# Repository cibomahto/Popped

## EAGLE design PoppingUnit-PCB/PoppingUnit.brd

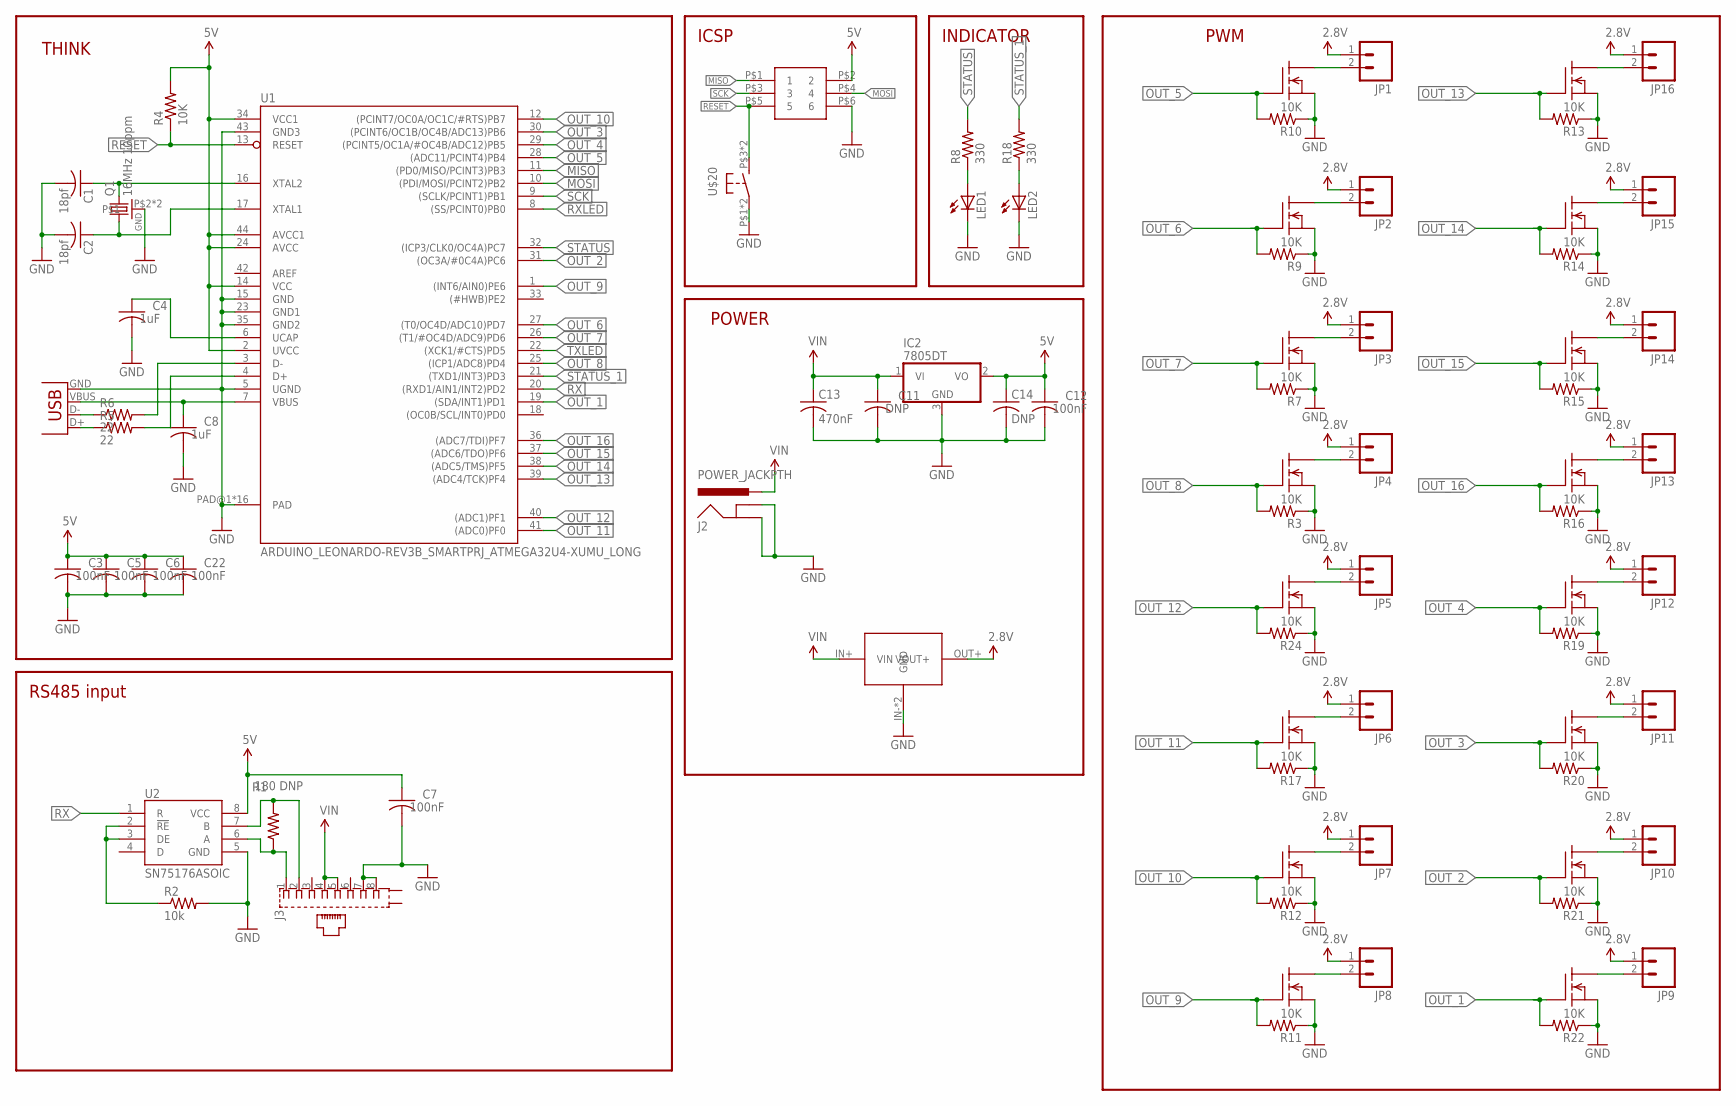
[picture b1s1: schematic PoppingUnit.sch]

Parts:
C1, C2: 18pf; C0603K
C3, C5, C6, C7, C12, C22: 100nF; C0603K
C4, C8: 1uF; C0603K
C11, C14: DNP; C0603K
C13: 470nF; C0603K
IC2: 7805DT; TO252
J2: POWER_JACKPTH; POWER_JACK_PTH
J3: 555153-1
JP1, JP2, JP3, JP4, JP5, JP6, JP7, JP8, JP9, JP10, JP11, JP12, JP13, JP14, JP15, JP16: M02-JST-2-PTH-NO_SILK; JST-2-PTH-NS
LED1, LED2: LED5MM
Q1: 16MHz 10ppm; CRSYTAL_2520
R1: 180 DNP; R0603
R2: 10k; R0603
R3, R4, R7, R9, R10, R11, R12, R13, R14, R15, R16, R17, R19, R20, R21, R22, R24: 10K; R0603
R5, R6: 22; R0603
R8, R18: 330; R0603
U1: ARDUINO_LEONARDO-REV3B_SMARTPRJ_ATMEGA32U4-XUMU_L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; QFN44ML7X7_LONGLEADS
U2: SN75176ASOIC; SO08
U$1, U$3, U$4, U$5, U$6, U$7, U$8, U$9, U$10, U$11, U$12, U$14, U$15, U$16, U$17, U$18: N_MOSFET; TO252
U$2: 2X3HEADER
U$19: DC_DC; DSN2596
U$20: BUTTON_MOMENTARY; BUTTON_MOMENTARY_KMR211G
X1: USBPTH; USB-B-PTH

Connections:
2.8V: JP1.1, JP2.1, JP3.1, JP4.1, JP5.1, JP6.1, JP7.1, JP8.1, JP9.1, JP10.1, JP11.1, JP12.1, JP13.1, JP14.1, JP15.1, JP16.1, U$19.OUT+ (VOUT+)
5V: C3.1, C5.1, C6.1, C7.1, C12.1, C14.1, C22.1, IC2.2 (VO), R4.2, U1.2 (UVCC), U1.14 (VCC), U1.24 (AVCC), U1.34 (VCC1), U1.44 (AVCC1), U2.8 (VCC), U$2.P$2 (2)
AREF: U1.42 (AREF)
CONNECT_ME: R2.1, U2.2 (!RE), U2.3 (DE)
GND: C1.2, C2.2, C3.2, C4.2, C5.2, C6.2, C7.2, C8.2, C11.2, C12.2, C13.2, C14.2, C22.2, IC2.3 (GND), J2.GND, J2.GNDBREAK, J3.7, J3.8, LED1.K (C), LED2.K (C), Q1.P$2, Q1.P$4, R2.2, R3.1, R7.1, R9.1, R10.1, R11.1, R12.1, R13.1, R14.1, R15.1, R16.1, R17.1, R19.1, R20.1, R21.1, R22.1, R24.1, U1.5 (UGND), U1.15 (GND), U1.23 (GND1), U1.35 (GND2), U1.43 (GND3), U1.PAD@1 (PAD), U1.PAD@2 (PAD), U1.PAD@3 (PAD), U1.PAD@4 (PAD), U1.PAD@5 (PAD), U1.PAD@6 (PAD), U1.PAD@7 (PAD), U1.PAD@8 (PAD), U1.PAD@9 (PAD), U1.PAD@10 (PAD), U1.PAD@11 (PAD), U1.PAD@12 (PAD), U1.PAD@13 (PAD), U1.PAD@14 (PAD), U1.PAD@15 (PAD), U1.PAD@16 (PAD), U2.5 (GND), U$1.P$2 (S), U$2.P$6 (6), U$3.P$2 (S), U$4.P$2 (S), U$5.P$2 (S), U$6.P$2 (S), U$7.P$2 (S), U$8.P$2 (S), U$9.P$2 (S), U$10.P$2 (S), U$11.P$2 (S), U$12.P$2 (S), U$14.P$2 (S), U$15.P$2 (S), U$16.P$2 (S), U$17.P$2 (S), U$18.P$2 (S), U$19.IN- (GND), U$19.OUT- (GND), U$20.P$1, U$20.P$2, X1.GND
MISO: U1.11 ((PD0/MISO/PCINT3)PB3), U$2.P$1 (1)
MOSI: U1.10 ((PDI/MOSI/PCINT2)PB2), U$2.P$4 (4)
unnamed: R6.1, X1.D-
unnamed: C1.1, Q1.P$3 (2), U1.16 (XTAL2)
unnamed: R5.1, X1.D+
unnamed: R5.2, U1.4 (D+)
unnamed: C2.1, Q1.P$1 (1), U1.17 (XTAL1)
unnamed: R6.2, U1.3 (D-)
unnamed: C8.1, U1.7 (VBUS), X1.VBUS
unnamed: LED1.A, R8.1
unnamed: C4.1, U1.6 (UCAP)
unnamed: JP11.2, U$16.P$3 (D)
unnamed: JP1.2, U$1.P$3 (D)
unnamed: LED2.A, R18.1
unnamed: JP2.2, U$3.P$3 (D)
unnamed: JP3.2, U$4.P$3 (D)
unnamed: JP4.2, U$5.P$3 (D)
unnamed: JP5.2, U$10.P$3 (D)
unnamed: JP6.2, U$11.P$3 (D)
unnamed: JP7.2, U$12.P$3 (D)
unnamed: JP8.2, U$14.P$3 (D)
unnamed: JP9.2, U$18.P$3 (D)
unnamed: JP10.2, U$17.P$3 (D)
unnamed: JP12.2, U$15.P$3 (D)
unnamed: JP13.2, U$9.P$3 (D)
unnamed: JP14.2, U$8.P$3 (D)
unnamed: JP15.2, U$7.P$3 (D)
unnamed: JP16.2, U$6.P$3 (D)
OUT_1: R22.2, U1.19 ((SDA/INT1)PD1), U$18.P$1 (G)
OUT_2: R21.2, U1.31 ((OC3A/#0C4A)PC6), U$17.P$1 (G)
OUT_3: R20.2, U1.30 ((PCINT6/OC1B/OC4B/ADC13)PB6), U$16.P$1 (G)
OUT_4: R19.2, U1.29 ((PCINT5/OC1A/#OC4B/ADC12)PB5), U$15.P$1 (G)
OUT_5: R10.2, U1.28 ((ADC11/PCINT4)PB4), U$1.P$1 (G)
OUT_6: R9.2, U1.27 ((T0/OC4D/ADC10)PD7), U$3.P$1 (G)
OUT_7: R7.2, U1.26 ((T1/#OC4D/ADC9)PD6), U$4.P$1 (G)
OUT_8: R3.2, U1.25 ((ICP1/ADC8)PD4), U$5.P$1 (G)
OUT_9: R11.2, U1.1 ((INT6/AIN0)PE6), U$14.P$1 (G)
OUT_10: R12.2, U1.12 ((PCINT7/OC0A/OC1C/#RTS)PB7), U$12.P$1 (G)
OUT_11: R17.2, U1.41 ((ADC0)PF0), U$11.P$1 (G)
OUT_12: R24.2, U1.40 ((ADC1)PF1), U$10.P$1 (G)
OUT_13: R13.2, U1.39 ((ADC4/TCK)PF4), U$6.P$1 (G)
OUT_14: R14.2, U1.38 ((ADC5/TMS)PF5), U$7.P$1 (G)
OUT_15: R15.2, U1.37 ((ADC6/TDO)PF6), U$8.P$1 (G)
OUT_16: R16.2, U1.36 ((ADC7/TDI)PF7), U$9.P$1 (G)
RESET: R4.1, U1.13 (RESET), U$2.P$5 (5), U$20.P$3 (S), U$20.P$4 (S)
RS485A: J3.1, R1.1, U2.6 (A)
RS485B: J3.2, R1.2, U2.7 (B)
RX: U1.20 ((RXD1/AIN1/INT2)PD2), U2.1 (R)
RXLED: U1.8 ((SS/PCINT0)PB0)
SCK: U1.9 ((SCLK/PCINT1)PB1), U$2.P$3 (3)
STATUS: R8.2, U1.32 ((ICP3/CLK0/OC4A)PC7)
STATUS_1: R18.2, U1.21 ((TXD1/INT3)PD3)
TXLED: U1.22 ((XCK1/#CTS)PD5)
VIN: C11.1, C13.1, IC2.1 (VI), J2.PWR, J3.4, J3.5, U$19.IN+ (VIN)

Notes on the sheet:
RS485 input
ICSP
INDICATOR
PWM
POWER
THINK

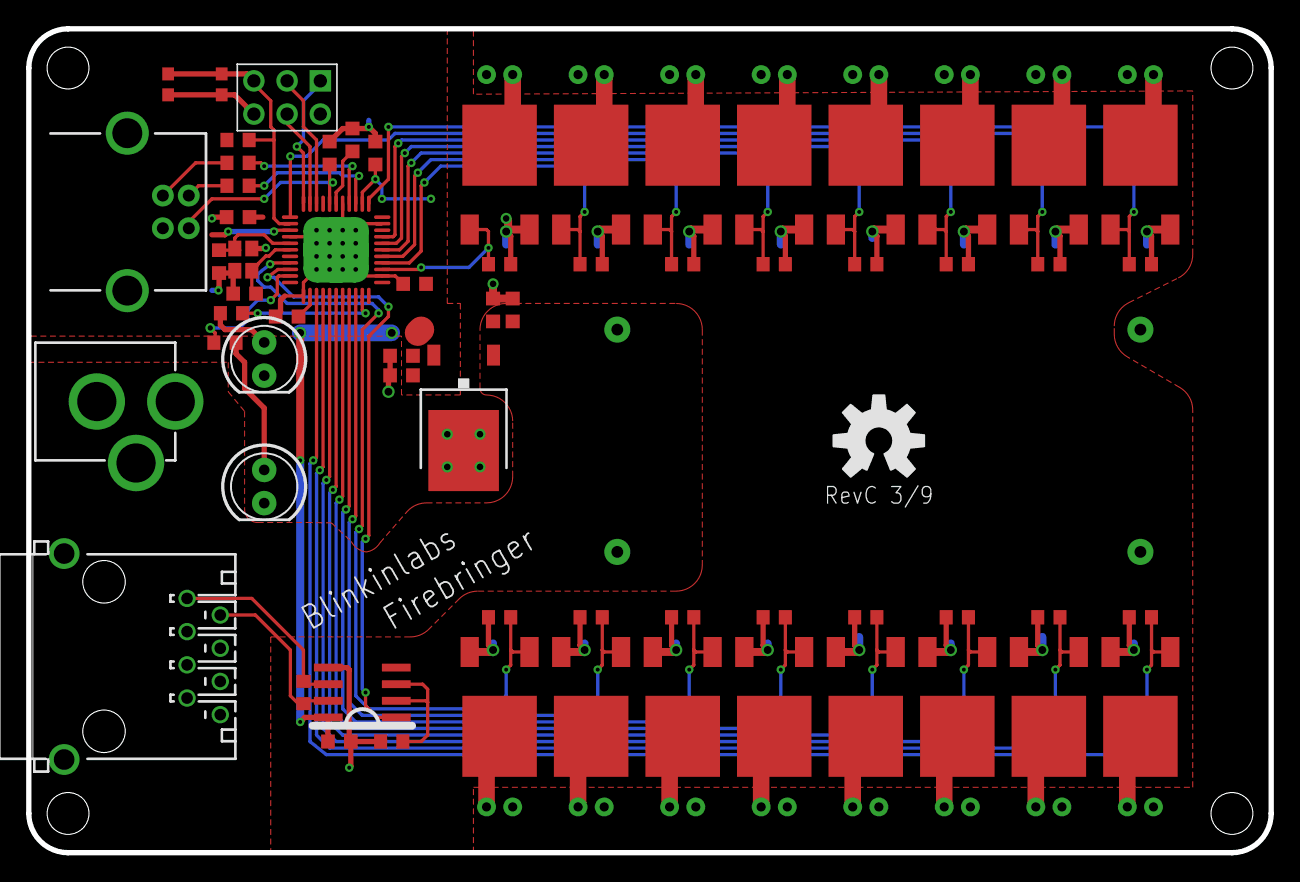
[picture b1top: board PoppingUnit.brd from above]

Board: 2 copper layers, 95.0 x 63.0 mm, 81 parts (0 on the bottom side), 56 nets.

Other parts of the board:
U$13: OSHW-LOGO-L

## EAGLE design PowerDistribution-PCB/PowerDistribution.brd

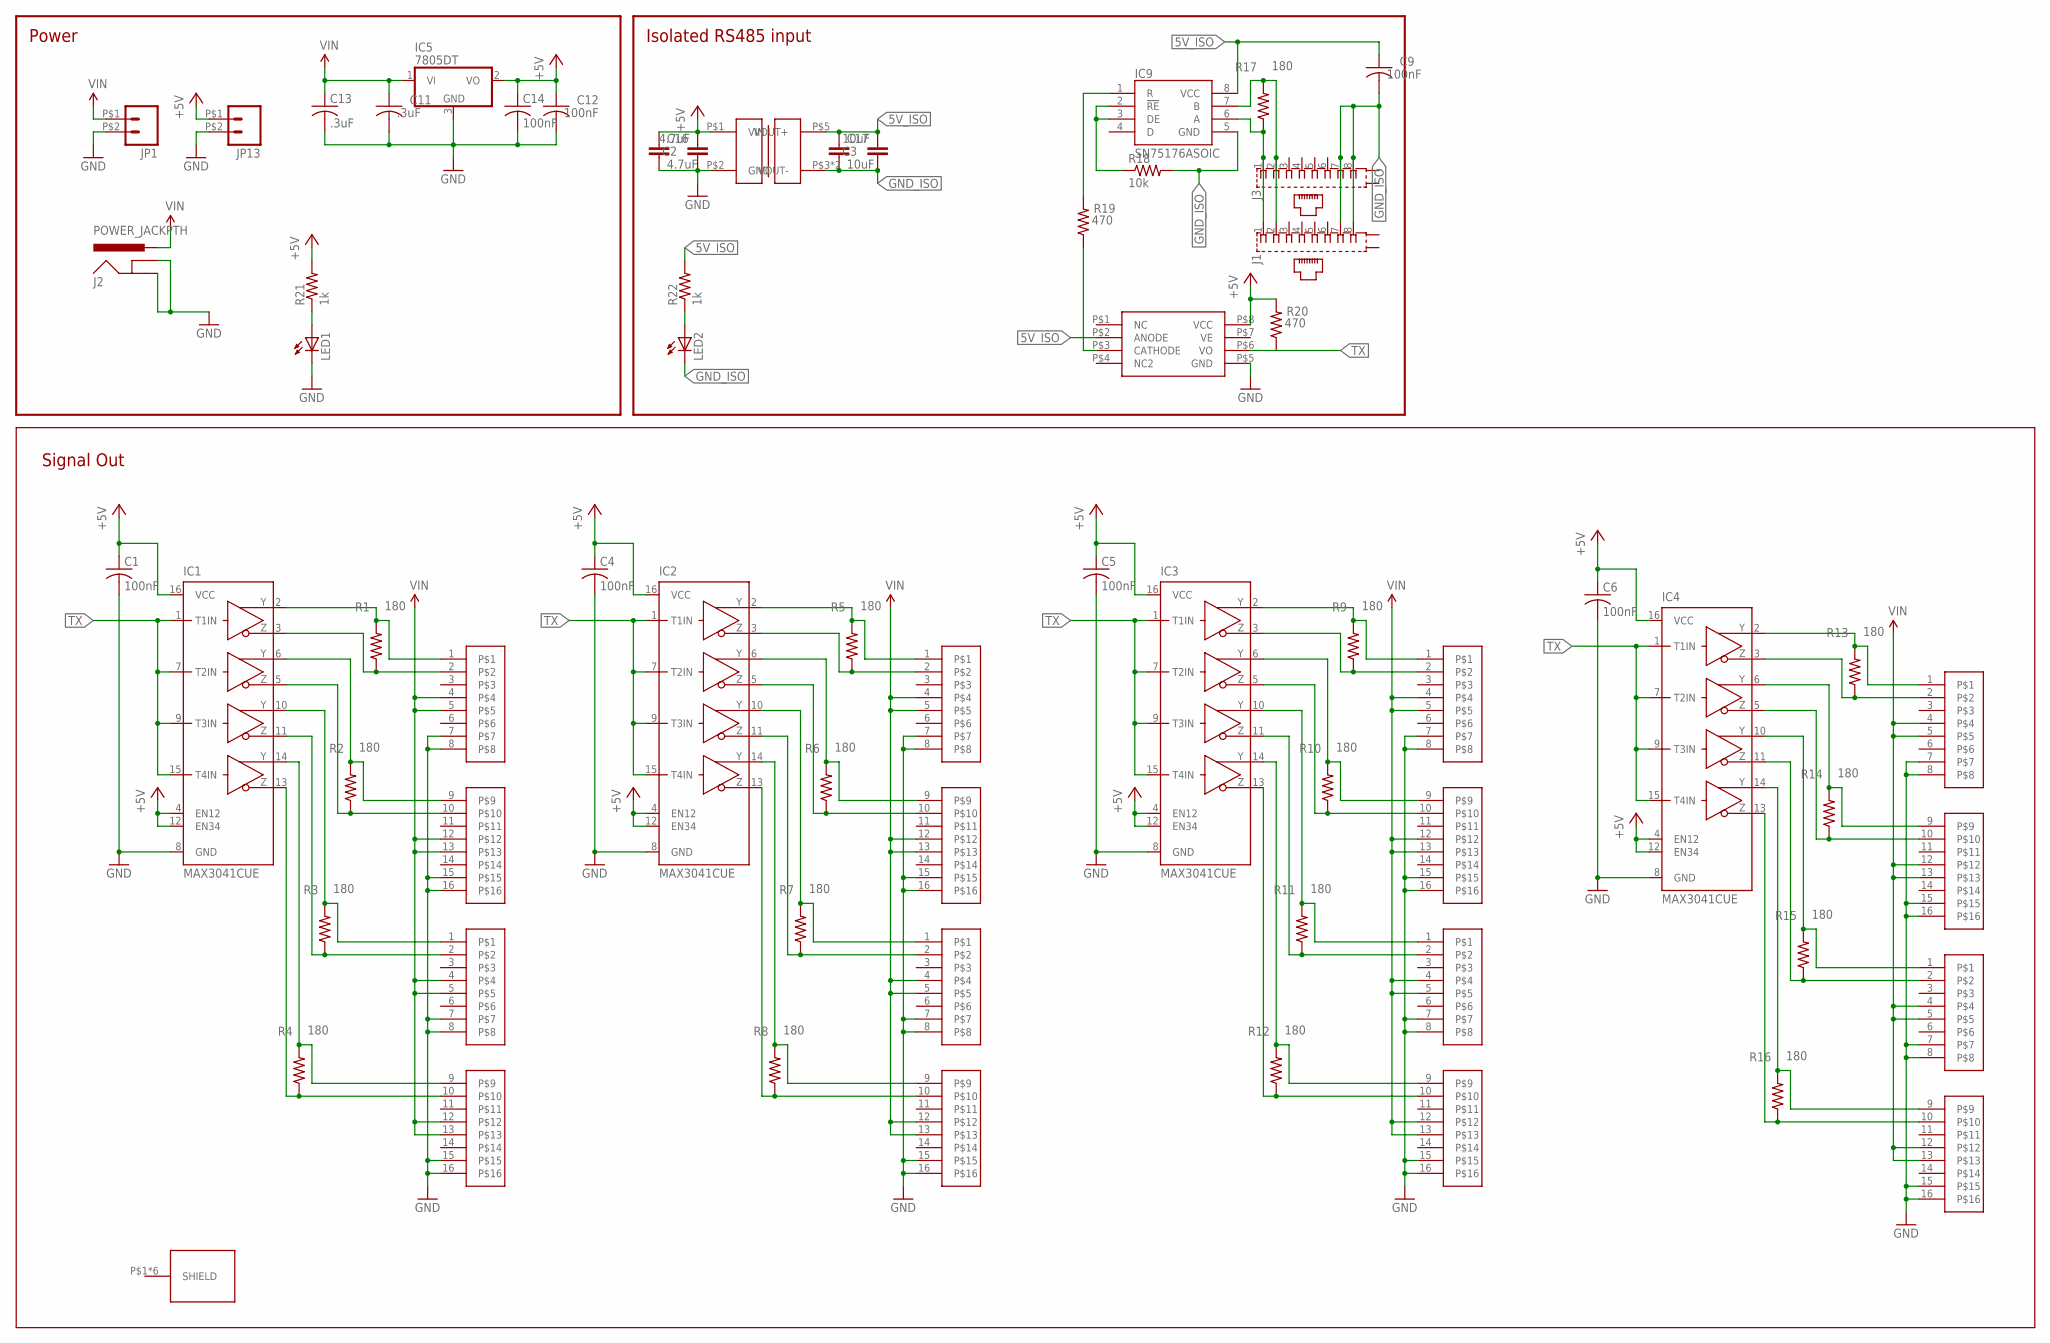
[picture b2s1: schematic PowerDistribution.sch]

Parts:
C1, C4, C5, C6, C9: 100nF; C0603
C2: 4.7uF; 0805
C3: 10uF; 0805
C11, C13: .3uF; C0603K
C12, C14: 100nF; C0603K
C16: 4.7uF; 1210
C17: 10uF; 1210
IC1, IC2, IC3, IC4: MAX3041CUE; TSSOP16
IC5: 7805DT; TO252
IC9: SN75176ASOIC; SO08
J1, J3: 555153-1
J2: POWER_JACKPTH; POWER_JACK_PTH
JP1, JP13: M026.35MM; SCREWTERMINAL-6.35MM-2
LED1, LED2: LED5MM
R1, R2, R3, R4, R5, R6, R7, R8, R9, R10, R11, R12, R13, R14, R15, R16, R17: 180; R0603
R18: 10k; R0603
R19, R20: 470; R0603
R21, R22: 1k; R0603
U$1, U$2, U$5, U$6, U$7, U$8, U$9, U$11: RJ45_8X2_JACK
U$3: 6N137; 8_SOIC
U$4: RJ45_8X2_BASE
U$10: DC_DC_ISOLATED_0505; IB_XLS-1W

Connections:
5V_ISO: C3.2, C9.1, C17.1, IC9.8 (VCC), R22.2, U$3.P$2 (ANODE), U$10.P$5 (VOUT+)
+5V: C1.1, C2.2, C4.1, C5.1, C6.1, C12.1, C14.1, C16.1, IC1.4 (EN12), IC1.12 (EN34), IC1.16 (VCC), IC2.4 (EN12), IC2.12 (EN34), IC2.16 (VCC), IC3.4 (EN12), IC3.12 (EN34), IC3.16 (VCC), IC4.4 (EN12), IC4.12 (EN34), IC4.16 (VCC), IC5.2 (VO), JP13.P$1 (1), R20.2, R21.2, U$3.P$8 (VCC), U$10.P$1 (VIN)
D9: IC9.2 (!RE), IC9.3 (DE), R18.1
GND: C1.2, C2.1, C4.2, C5.2, C6.2, C11.2, C12.2, C13.2, C14.2, C16.2, IC1.8 (GND), IC2.8 (GND), IC3.8 (GND), IC4.8 (GND), IC5.3 (GND), J2.GND, J2.GNDBREAK, JP1.P$2 (2), JP13.P$2 (2), LED1.K (C), U$1.7, U$1.8, U$1.15, U$1.16, U$2.7, U$2.8, U$2.15, U$2.16, U$3.P$5 (GND), U$5.7, U$5.8, U$5.15, U$5.16, U$6.7, U$6.8, U$6.15, U$6.16, U$7.7, U$7.8, U$7.15, U$7.16, U$8.7, U$8.8, U$8.15, U$8.16, U$9.7, U$9.8, U$9.15, U$9.16, U$10.P$2 (GND), U$11.7, U$11.8, U$11.15, U$11.16
GND_ISO: C3.1, C9.2, C17.2, IC9.5 (GND), J1.7, J1.8, J3.7, J3.8, LED2.K (C), R18.2, U$10.P$3 (VOUT-), U$10.P$4 (VOUT-)
unnamed: R19.1, U$3.P$3 (CATHODE)
unnamed: IC1.2 (Y1), R1.2, U$5.1
unnamed: IC9.1 (R), R19.2
unnamed: IC1.3 (Z1), R1.1, U$5.2
unnamed: IC1.13 (Z4), R4.1, U$8.10
unnamed: IC1.14 (Y4), R4.2, U$8.9
unnamed: IC1.11 (Z3), R3.1, U$8.2
unnamed: IC2.2 (Y1), R5.2, U$1.1
unnamed: IC1.10 (Y3), R3.2, U$8.1
unnamed: IC1.5 (Z2), R2.1, U$5.10
unnamed: IC1.6 (Y2), R2.2, U$5.9
unnamed: IC2.3 (Z1), R5.1, U$1.2
unnamed: IC2.13 (Z4), R8.1, U$2.10
unnamed: IC2.14 (Y4), R8.2, U$2.9
unnamed: IC2.11 (Z3), R7.1, U$2.2
unnamed: IC2.5 (Z2), R6.1, U$1.10
unnamed: IC2.6 (Y2), R6.2, U$1.9
unnamed: IC2.10 (Y3), R7.2, U$2.1
unnamed: IC3.2 (Y1), R9.2, U$6.1
unnamed: IC3.3 (Z1), R9.1, U$6.2
unnamed: IC3.13 (Z4), R12.1, U$7.10
unnamed: IC3.14 (Y4), R12.2, U$7.9
unnamed: IC3.11 (Z3), R11.1, U$7.2
unnamed: IC3.5 (Z2), R10.1, U$6.10
unnamed: IC3.6 (Y2), R10.2, U$6.9
unnamed: IC3.10 (Y3), R11.2, U$7.1
unnamed: IC4.2 (Y1), R13.2, U$9.1
unnamed: IC4.3 (Z1), R13.1, U$9.2
unnamed: IC4.13 (Z4), R16.1, U$11.10
unnamed: IC4.14 (Y4), R16.2, U$11.9
unnamed: IC4.11 (Z3), R15.1, U$11.2
unnamed: IC4.5 (Z2), R14.1, U$9.10
unnamed: IC4.6 (Y2), R14.2, U$9.9
unnamed: IC4.10 (Y3), R15.2, U$11.1
unnamed: LED1.A, R21.1
unnamed: LED2.A, R22.1
RS485A9: IC9.6 (A), J1.1, J3.1, R17.1
RS485B9: IC9.7 (B), J1.2, J3.2, R17.2
TX: IC1.1 (T1IN), IC1.7 (T2IN), IC1.9 (T3IN), IC1.15 (T4IN), IC2.1 (T1IN), IC2.7 (T2IN), IC2.9 (T3IN), IC2.15 (T4IN), IC3.1 (T1IN), IC3.7 (T2IN), IC3.9 (T3IN), IC3.15 (T4IN), IC4.1 (T1IN), IC4.7 (T2IN), IC4.9 (T3IN), IC4.15 (T4IN), R20.1, U$3.P$6 (VO)
VIN: C11.1, C13.1, IC5.1 (VI), J2.PWR, JP1.P$1 (1), U$1.4, U$1.5, U$1.12, U$1.13, U$2.4, U$2.5, U$2.12, U$2.13, U$5.4, U$5.5, U$5.12, U$5.13, U$6.4, U$6.5, U$6.12, U$6.13, U$7.4, U$7.5, U$7.12, U$7.13, U$8.4, U$8.5, U$8.12, U$8.13, U$9.4, U$9.5, U$9.12, U$9.13, U$11.4, U$11.5, U$11.12, U$11.13

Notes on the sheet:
Isolated RS485 input
Signal Out
Power

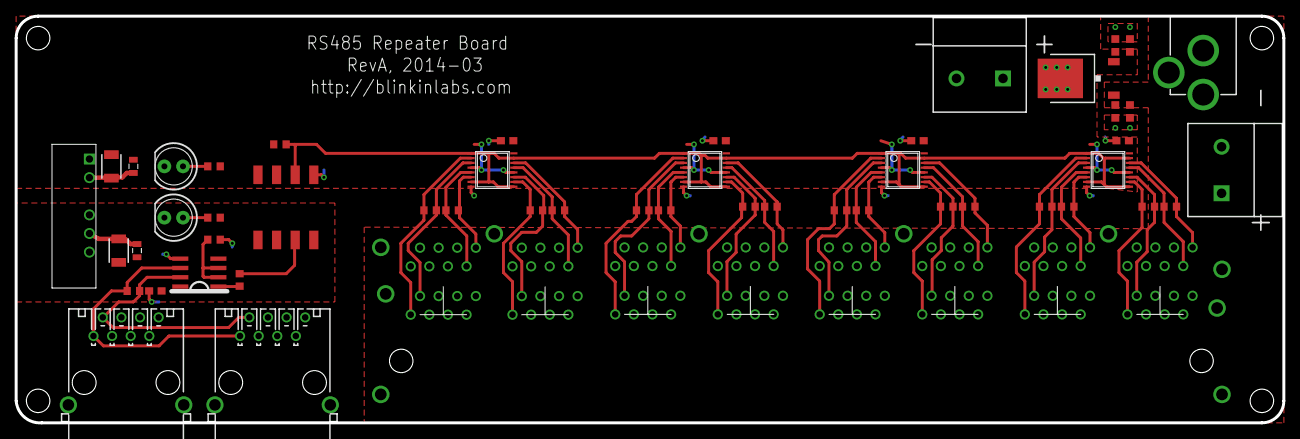
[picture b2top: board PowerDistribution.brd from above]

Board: 2 copper layers, 173.0 x 55.5 mm, 59 parts (0 on the bottom side), 45 nets.

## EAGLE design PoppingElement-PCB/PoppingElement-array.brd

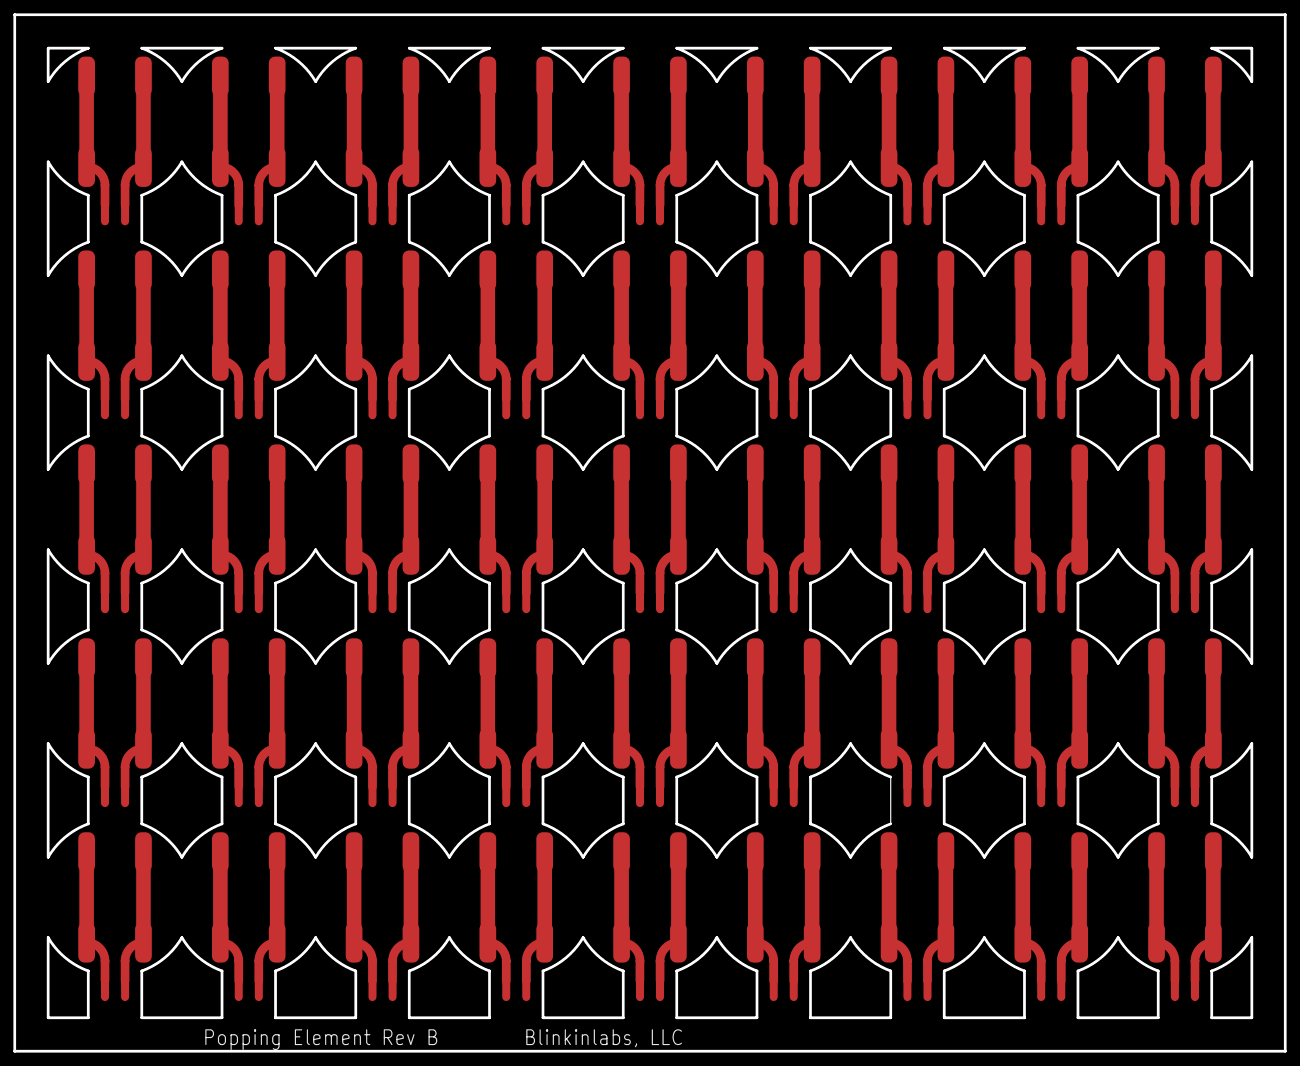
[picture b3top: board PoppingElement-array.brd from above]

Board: 2 copper layers, 190.0 x 155.0 mm, 90 parts (0 on the bottom side), 90 nets.

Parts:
U$1, U$5, U$7, U$9, U$11, U$13, U$15, U$17, U$19, U$21, U$23, U$25, U$27, U$29, U$31, U$33, U$35, U$37, U$39, U$41, U$43, U$45, U$47, U$49, U$51, U$53, U$55, U$57, U$59, U$61, U$63, U$65, U$67, U$69, U$71, U$73, U$75, U$77, U$79, U$81, U$83, U$85, U$87, U$89, U$91: CIGARETTE_LIGHTER
U$2, U$6, U$8, U$10, U$12, U$14, U$16, U$18, U$20, U$22, U$24, U$26, U$28, U$30, U$32, U$34, U$36, U$38, U$40, U$42, U$44, U$46, U$48, U$50, U$52, U$54, U$56, U$58, U$60, U$62, U$64, U$66, U$68, U$70, U$72, U$74, U$76, U$78, U$80, U$82, U$84, U$86, U$88, U$90, U$92: M02; PADS_2MMX2

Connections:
unnamed: U$1.P$1, U$1.P$3, U$2.P$2
unnamed: U$1.P$2, U$1.P$4, U$2.P$1
unnamed: U$5.P$1, U$5.P$3, U$6.P$2
unnamed: U$5.P$2, U$5.P$4, U$6.P$1
unnamed: U$7.P$1, U$7.P$3, U$8.P$2
unnamed: U$7.P$2, U$7.P$4, U$8.P$1
unnamed: U$9.P$1, U$9.P$3, U$10.P$2
unnamed: U$9.P$2, U$9.P$4, U$10.P$1
unnamed: U$11.P$1, U$11.P$3, U$12.P$2
unnamed: U$11.P$2, U$11.P$4, U$12.P$1
unnamed: U$13.P$1, U$13.P$3, U$14.P$2
unnamed: U$13.P$2, U$13.P$4, U$14.P$1
unnamed: U$15.P$1, U$15.P$3, U$16.P$2
unnamed: U$15.P$2, U$15.P$4, U$16.P$1
unnamed: U$21.P$1, U$21.P$3, U$22.P$2
unnamed: U$17.P$1, U$17.P$3, U$18.P$2
unnamed: U$17.P$2, U$17.P$4, U$18.P$1
unnamed: U$19.P$1, U$19.P$3, U$20.P$2
unnamed: U$19.P$2, U$19.P$4, U$20.P$1
unnamed: U$21.P$2, U$21.P$4, U$22.P$1
unnamed: U$31.P$1, U$31.P$3, U$32.P$2
unnamed: U$23.P$1, U$23.P$3, U$24.P$2
unnamed: U$23.P$2, U$23.P$4, U$24.P$1
unnamed: U$25.P$1, U$25.P$3, U$26.P$2
unnamed: U$25.P$2, U$25.P$4, U$26.P$1
unnamed: U$27.P$1, U$27.P$3, U$28.P$2
unnamed: U$27.P$2, U$27.P$4, U$28.P$1
unnamed: U$29.P$1, U$29.P$3, U$30.P$2
unnamed: U$29.P$2, U$29.P$4, U$30.P$1
unnamed: U$31.P$2, U$31.P$4, U$32.P$1
unnamed: U$33.P$1, U$33.P$3, U$34.P$2
unnamed: U$33.P$2, U$33.P$4, U$34.P$1
unnamed: U$35.P$1, U$35.P$3, U$36.P$2
unnamed: U$35.P$2, U$35.P$4, U$36.P$1
unnamed: U$37.P$1, U$37.P$3, U$38.P$2
unnamed: U$37.P$2, U$37.P$4, U$38.P$1
unnamed: U$39.P$1, U$39.P$3, U$40.P$2
unnamed: U$39.P$2, U$39.P$4, U$40.P$1
unnamed: U$41.P$1, U$41.P$3, U$42.P$2
unnamed: U$41.P$2, U$41.P$4, U$42.P$1
unnamed: U$43.P$1, U$43.P$3, U$44.P$2
unnamed: U$43.P$2, U$43.P$4, U$44.P$1
unnamed: U$45.P$1, U$45.P$3, U$46.P$2
unnamed: U$45.P$2, U$45.P$4, U$46.P$1
unnamed: U$47.P$1, U$47.P$3, U$48.P$2
unnamed: U$47.P$2, U$47.P$4, U$48.P$1
unnamed: U$49.P$1, U$49.P$3, U$50.P$2
unnamed: U$49.P$2, U$49.P$4, U$50.P$1
unnamed: U$51.P$1, U$51.P$3, U$52.P$2
unnamed: U$51.P$2, U$51.P$4, U$52.P$1
unnamed: U$53.P$1, U$53.P$3, U$54.P$2
unnamed: U$53.P$2, U$53.P$4, U$54.P$1
unnamed: U$55.P$1, U$55.P$3, U$56.P$2
unnamed: U$55.P$2, U$55.P$4, U$56.P$1
unnamed: U$57.P$1, U$57.P$3, U$58.P$2
unnamed: U$57.P$2, U$57.P$4, U$58.P$1
unnamed: U$59.P$1, U$59.P$3, U$60.P$2
unnamed: U$59.P$2, U$59.P$4, U$60.P$1
unnamed: U$61.P$1, U$61.P$3, U$62.P$2
unnamed: U$61.P$2, U$61.P$4, U$62.P$1
unnamed: U$63.P$1, U$63.P$3, U$64.P$2
unnamed: U$63.P$2, U$63.P$4, U$64.P$1
unnamed: U$65.P$1, U$65.P$3, U$66.P$2
unnamed: U$65.P$2, U$65.P$4, U$66.P$1
unnamed: U$67.P$1, U$67.P$3, U$68.P$2
unnamed: U$67.P$2, U$67.P$4, U$68.P$1
unnamed: U$69.P$1, U$69.P$3, U$70.P$2
unnamed: U$69.P$2, U$69.P$4, U$70.P$1
unnamed: U$71.P$1, U$71.P$3, U$72.P$2
unnamed: U$71.P$2, U$71.P$4, U$72.P$1
unnamed: U$73.P$1, U$73.P$3, U$74.P$2
unnamed: U$73.P$2, U$73.P$4, U$74.P$1
unnamed: U$75.P$1, U$75.P$3, U$76.P$2
unnamed: U$75.P$2, U$75.P$4, U$76.P$1
unnamed: U$77.P$1, U$77.P$3, U$78.P$2
unnamed: U$77.P$2, U$77.P$4, U$78.P$1
unnamed: U$79.P$1, U$79.P$3, U$80.P$2
unnamed: U$79.P$2, U$79.P$4, U$80.P$1
unnamed: U$81.P$1, U$81.P$3, U$82.P$2
unnamed: U$81.P$2, U$81.P$4, U$82.P$1
unnamed: U$83.P$1, U$83.P$3, U$84.P$2
unnamed: U$83.P$2, U$83.P$4, U$84.P$1
unnamed: U$85.P$1, U$85.P$3, U$86.P$2
unnamed: U$85.P$2, U$85.P$4, U$86.P$1
unnamed: U$87.P$1, U$87.P$3, U$88.P$2
unnamed: U$87.P$2, U$87.P$4, U$88.P$1
unnamed: U$89.P$1, U$89.P$3, U$90.P$2
unnamed: U$89.P$2, U$89.P$4, U$90.P$1
unnamed: U$91.P$1, U$91.P$3, U$92.P$2
unnamed: U$91.P$2, U$91.P$4, U$92.P$1

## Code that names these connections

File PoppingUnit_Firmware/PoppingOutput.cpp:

#include "PoppingOutput.h"

uint8_t outputPins[OUTPUT_COUNT] = {
   2, // PD1- Output 1
   5, // PC6- Output 2
  10, // PB6- Output 3
   9, // PB5- Output 4
   8, // PB4- Output 5
   6, // PD7- Output 6
  12, // PD6- Output 7
   4, // PD4- Output 8 
   7, // PE6- Output 9
  11, // PB7- Output 10
  23, // PF0- Output 11
  22, // PF1- Output 12
  21, // PF4- Output 13
  20, // PF5- Output 14
  19, // PF6- Output 15
  18, // PF7- Output 16
};

void PoppingOutput::init() {
  for(uint8_t output = 0; output < OUTPUT_COUNT; output++) {
    pinMode(outputPins[output], OUTPUT);
    digitalWrite(outputPins[output], LOW);
    
    popExpireTime[output] = 0;
    isPopping[output] = false;
  }
  
  // PIN_STATUS_1_LED conflicts with the USART TX pin, so we need to disable that function.
  UCSR1B &= ~(1<<TXEN1);
  pinMode(PIN_STATUS_1_LED, OUTPUT);
  digitalWrite(PIN_STATUS_1_LED, LOW);
}

uint8_t PoppingOutput::getPopCount() {
  uint8_t count = 0;
  
  for(uint8_t output = 0; output < OUTPUT_COUNT; output++) {  
    if(isPopping[output]) {
      count++;
    }
  }

  return count;
}

void PoppingOutput::update() {
  for(uint8_t output = 0; output < OUTPUT_COUNT; output++) {
    if(isPopping[output]) {
      if(millis() > popExpireTime[output]) {
        digitalWrite(outputPins[output], LOW);
        isPopping[output] = false;
      }
    }
  }
    
  if(getPopCount() == 0) {
    digitalWrite(PIN_STATUS_1_LED, LOW);
  }
}


void PoppingOutput::pop(uint8_t output, uint32_t time) {
  // If we aren't already popping the maximum outputs,
  // and this is a valid output
  if(output < OUTPUT_COUNT
     && getPopCount() < MAX_CONCURRENT_POPS) {

    // Clip the time to the maximum
    if(time > MAX_POP_TIME) {
      time = MAX_POP_TIME;
    }
       
    // If this output isn't already being popped
    if(isPopping[output] == false) {
      popExpireTime[output] = millis() + time;
      isPopping[output] = true;
      digitalWrite(outputPins[output], HIGH);
      digitalWrite(PIN_STATUS_1_LED, HIGH);
    }
  }
}

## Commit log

2014-03-05 Initial commit, PCB design for the Popping Unit and Popping Element
2014-03-05 Add Popping unit case design, as sent for quote
2014-03-08 Update popping unit to RevB (should be good to go!)
2014-03-08 Add firmware for the Popping Unit
2014-03-08 Add TODO file to PCB
2014-03-08 First draft of power distribution PCB
2014-03-08 Update Popping Unit PCB for release, send to board house
2014-03-08 Finish routing power distribution PCB; still need to fit to case
2014-03-08 Update popping unit firmware to support simple message protocol (seems to work!)
2014-03-08 Power Distribution: Finish layout, add mouting holes at edges (likely not quite enough), release RevA
2014-03-09 Update PoppingUnit board to fix bummer mistake (Arduino remuxes TX, so don't use it as an output channel), update firmware to match
2014-03-09 Add simple Processing debug example
2014-03-11 RevC of the Popping Element case
2014-03-11 Updates to firmware: Separate update() function to avoid crashes
2014-03-11 Update CAM job to output vscore on GM3
2014-03-11 Update Output test example to support varying the pop time
2014-03-11 Add Popping Unit board, RevC (manufacturing version)
2014-03-11 Add array version of the popping element, and foam outline
2014-03-11 Ignore temporary files
2014-03-11 Rename PoppingUnit firmware
2014-03-11 Fix the name of the popping unit case
2014-03-14 Rename Poppingunit firmware; arduino can't handle a -
2014-03-14 Rename eagle job
2014-03-24 Add big grid to enable popping of all 35 units
2014-03-24 Firmware update: Attempt to prevent glitch in status led
2014-03-24 Update schematic with production component values
2014-03-25 Update comments, small cleanups. Status LED glitch is fixed.
2014-04-03 Add sequenced playback support
2014-04-04 Latest pass, add per-command delays

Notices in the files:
parts and their libraries:
SparkFun-Connectors: Licensing: CC v3.0 Share-Alike You are welcome to use this library for commercial purposes.
